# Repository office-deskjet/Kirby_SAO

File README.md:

# Kirby_SAO

Shitty Addon for Defcon 27.

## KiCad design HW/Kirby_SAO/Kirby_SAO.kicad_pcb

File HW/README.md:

# Notes

Make a directory called project_name.pretty and put footprint files and libraires in here.  
Copy in the footprints from inkscape and other projects

Preferences > Manage Footprint Libraries > Project Specific Libraries  
click folder icon and navigate to file. it will use the KIPRJMOD variable for path

Preferences > Manage Footprint Libraries > Project Specific Footprints  
click folder icon and navigate to .pretty directory. 

import schematic  

## Layout
Copy paste the edgecuts from the output pcb file made my svg2shenzhen into the project pcb file  
cursour location is shown on bottum right of Pcbnew window.  
the origin will be at 0,0.  
Select all the edge cuts and center the mouse on 0,0.  
Press M to move the edge.cuts to 100, 100.  
Press E to edit the footprint and set its X,Y to 100, 100  
After the footprint is place, lock it so you dont acidently move it. press L   

# Parts
[LEDs](https://katalog.we-online.com/led/datasheet/155124RS73200A.pdf)

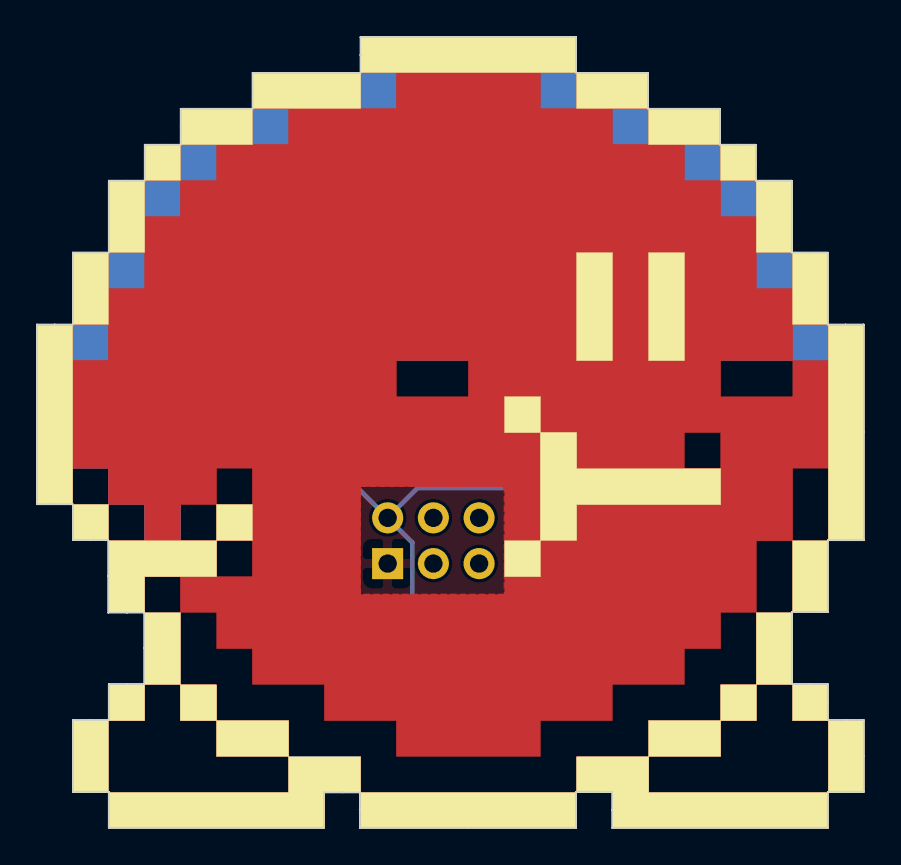
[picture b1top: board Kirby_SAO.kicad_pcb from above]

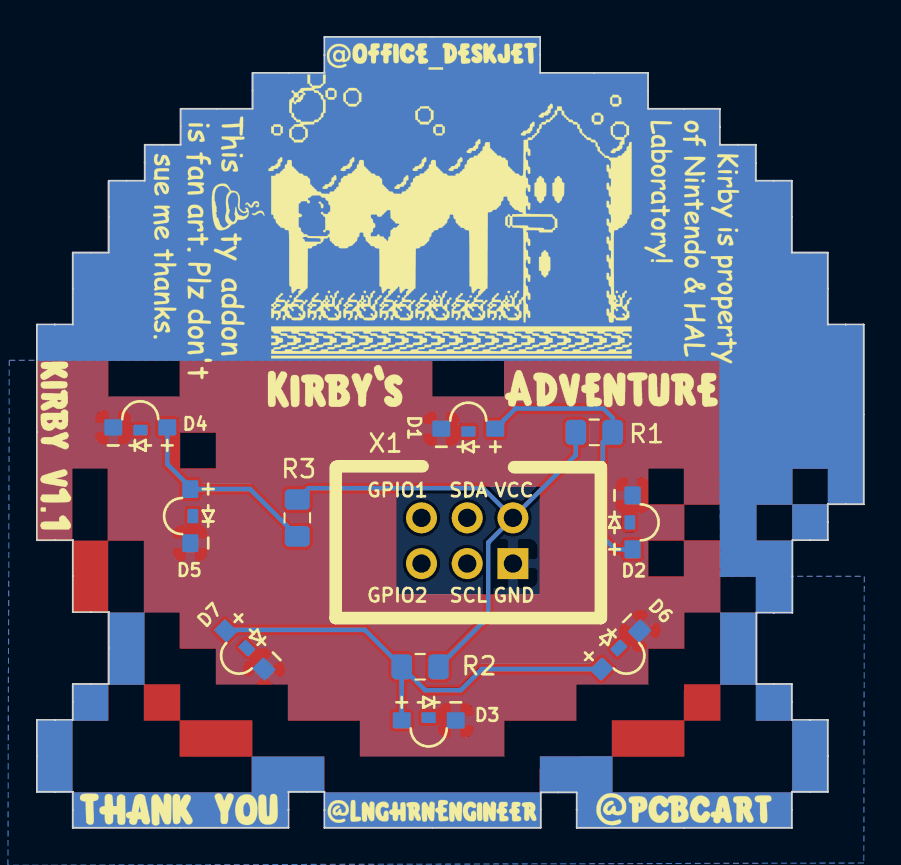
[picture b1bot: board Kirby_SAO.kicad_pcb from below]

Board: 2 copper layers, 45.9 x 43.9 mm, 11 parts (10 on the bottom side), 5 nets.

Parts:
D1, D2, D3, D4, D5, D6, D7: LED; 1204_SIDE_VIEW_LED
R1, R2, R3: 50R; R_0805_2012Metric_Pad1.15x1.40mm_HandSolder
X1: Badgelife_sao_connector_v169bis; Badgelife-SAOv169-SAO-2x3

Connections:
GND: D1.1, D2.1, D3.1, D4.1, D5.1, D6.1, D7.1, X1.2
unnamed: D1.2, D2.2, R1.2
unnamed: D3.2, D6.2, D7.2, R2.2
unnamed: D4.2, D5.2, R3.2
VCC: R1.1, R2.1, R3.1, X1.1

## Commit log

2019-05-21 first
2019-05-22 Readme
2019-05-22 adding notes and art layers
2019-05-22 Silk, F.Cu layers done
2019-05-22 Added F.Mask
2019-05-22 BUGS: edgcut exports to the wrong scaled size, F.Cu layer not exporting
2019-05-22 F.Cu exports now with threshold set to 100
2019-05-22 Edge cuts not scaled correctly still
2019-05-22 Fixed the board edge cut layer
2019-05-23 Adding KiCad Project and notes
2019-05-23 Adding Footprints and config paths for footprint and library
2019-05-23 coppied wrong files over, removing them and adding correct footprints
2019-05-23 added schematic, footprints, netlist
2019-05-23 added footprints
2019-05-23 updating doc
2019-05-23 doc cleanup
2019-05-23 moving around LEDs
2019-05-24 Added more LEDs, Working on Art layout
2019-05-24 finsihed up B.Mask
2019-06-01 stuff changed
2019-06-03 Finialize F.Cu F.Silk F.Mask B.Mask Edge.Cuts. Added resistors to schematic and make netlist.
2019-06-03 Fixed wiring in schematic, generate netlist. Added 3D model for LED. Updated footprints for board layers. impported netlist and footprints to PCBnew
2019-06-03 Places LEDs Added B.Cu keepout
2019-06-03 B.Cu ground pour.
2019-06-03 Added B.Cu footprint and SVG artwork
2019-06-03 Fixed F.Cu
2019-06-03 Added negative copper art
2019-06-03 fix ART README
2019-06-06 working on B.Silk art
2019-06-07 Added B.Silk art and text
2019-06-07 Change resistors to 50R
2019-06-07 Finish B.Silk. Updated PCB with new silk and resistor layout
2019-06-07 B.Silk art and text
2019-07-01 B.Skilk and B.Cu updates
2019-07-01 added B.Mask Kirby
2019-07-01 updating B.Mask
2019-07-02 finial
